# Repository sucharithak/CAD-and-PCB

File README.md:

# COMSOL- CAD-and-PCB
I created this repository to show the CAD and PCB designs I made during my student life as a hiwi. And I updated it with my recent COMSOL designs
This work was done over a span of few years.
I have learnt and unlearnt doing designs under many informative tutors, a.k.a my PHD and postdoc colleagues from the labs I have worked.
The main motivation in creating this repository is to include all my designs at a single place so that I can put a link in my CV.

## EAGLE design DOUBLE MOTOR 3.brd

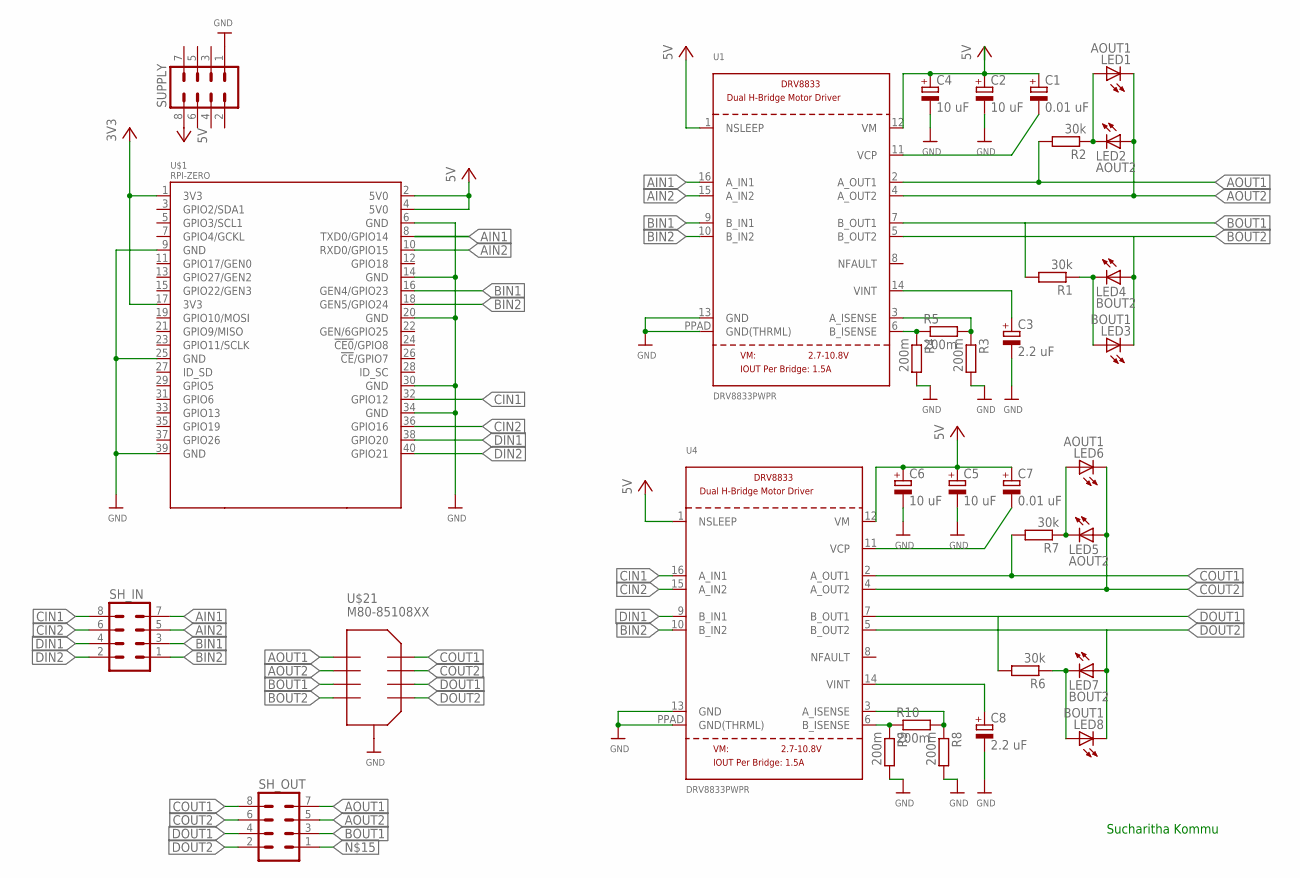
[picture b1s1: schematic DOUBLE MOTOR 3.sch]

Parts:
C1, C7: 0.01 uF; SMC_C
C2, C5: 10 uF; E2,5-6
C3, C8: 2.2 uF; SMC_C
C4, C6: 10 uF; E3,5-8
LED1, LED6: AOUT1; LED5MM
LED2, LED5: AOUT2; LED5MM
LED3, LED8: BOUT1; LED5MM
LED4, LED7: BOUT2; LED5MM
R1, R2, R6, R7: 30k; 0204V
R3, R4, R5, R8, R9, R10: 200m; 0204V
SH_IN: MA04-2
SH_OUT: MA04-2
SUPPLY: MA04-2
U1, U4: DRV8833PWPR; HTSSOP16
U$1: RPI-ZERO; RASPBERRYPI_BASTELSTUBE_V13_RASPI_BOARD_B+_FULL
U$21: M80-85108XX

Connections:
3V3: U$1.1 (3V3), U$1.17 (3V3)
5V: U$1.2 (5V0), U$1.4 (5V0)
AIN1: SH_IN.7, U1.16 (A_IN1), U$1.8 (TXD0/GPIO14)
AIN2: SH_IN.5, U1.15 (A_IN2), U$1.10 (RXD0/GPIO15)
AOUT1: R2.2, SH_OUT.7, U1.2 (A_OUT1), U$21.P$5
AOUT2: LED1.K (C), LED2.A, SH_OUT.5, U1.4 (A_OUT2), U$21.P$7
BIN1: SH_IN.3, U1.9 (B_IN1), U$1.16 (GEN4/GPIO23)
BIN2: SH_IN.1, U1.10 (B_IN2), U4.10 (B_IN2), U$1.18 (GEN5/GPIO24)
BOUT1: R1.2, SH_OUT.3, U1.7 (B_OUT1), U$21.P$9
BOUT2: LED3.K (C), LED4.A, U1.5 (B_OUT2), U$21.P$11
CIN1: SH_IN.8, U4.16 (A_IN1), U$1.32 (GPIO12)
CIN2: SH_IN.6, U4.15 (A_IN2), U$1.36 (GPIO16)
COUT1: R7.2, SH_OUT.8, U4.2 (A_OUT1), U$21.P$6
COUT2: LED5.A, LED6.K (C), SH_OUT.6, U4.4 (A_OUT2), U$21.P$8
DIN1: SH_IN.4, U4.9 (B_IN1), U$1.38 (GPIO20)
DIN2: SH_IN.2, U$1.40 (GPIO21)
DOUT1: R6.2, SH_OUT.4, U4.7 (B_OUT1), U$21.P$10
DOUT2: LED7.A, LED8.K (C), SH_OUT.2, U4.5 (B_OUT2), U$21.P$12
GND: C1.-, C2.-, C3.-, C4.-, C5.-, C6.-, C7.-, C8.-, R3.2, R4.2, R8.2, R9.2, SUPPLY.1, U1.11 (VCP), U1.13 (GND), U1.PPAD (GND(THRML)), U4.11 (VCP), U4.13 (GND), U4.PPAD (GND(THRML)), U$1.6 (GND), U$1.9 (GND), U$1.14 (GND), U$1.20 (GND), U$1.25 (GND), U$1.30 (GND), U$1.34 (GND), U$1.39 (GND), U$21.COMMON1 (COMMON), U$21.COMMON2 (COMMON), U$21.COMMON3 (COMMON), U$21.COMMON4 (COMMON)
unnamed: LED7.K (C), LED8.A, R6.1
unnamed: LED5.K (C), LED6.A, R7.1
unnamed: R8.1, R10.2, U4.3 (A_ISENSE)
unnamed: C8.+, U4.14 (VINT)
unnamed: LED1.A, LED2.K (C), R2.1
unnamed: R9.1, R10.1, U4.6 (B_ISENSE)
unnamed: LED3.A, LED4.K (C), R1.1
unnamed: C3.+, U1.14 (VINT)
unnamed: R3.1, R5.2, U1.3 (A_ISENSE)
unnamed: R4.1, R5.1, U1.6 (B_ISENSE)
VCC: C1.+, C2.+, C4.+, C5.+, C6.+, C7.+, SUPPLY.8, U1.1 (NSLEEP), U1.12 (VM), U4.1 (NSLEEP), U4.12 (VM)

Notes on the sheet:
Sucharitha Kommu

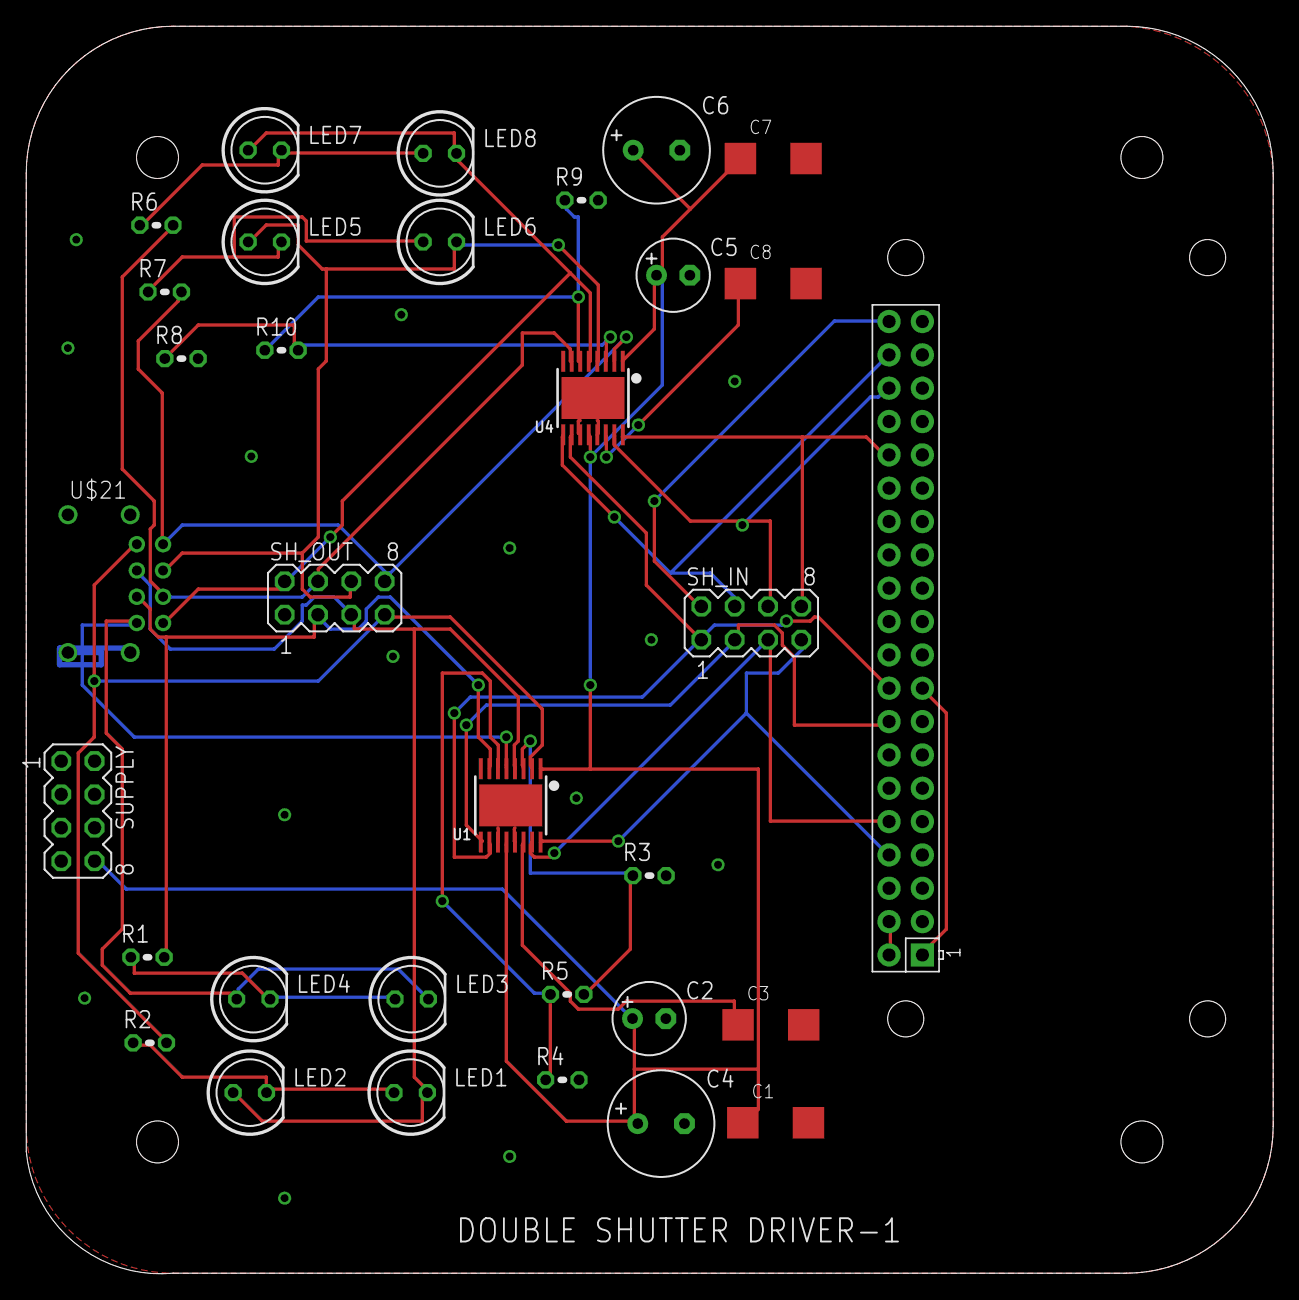
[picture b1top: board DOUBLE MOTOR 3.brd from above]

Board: 2 copper layers, 95.0 x 95.0 mm, 33 parts (0 on the bottom side), 30 nets.

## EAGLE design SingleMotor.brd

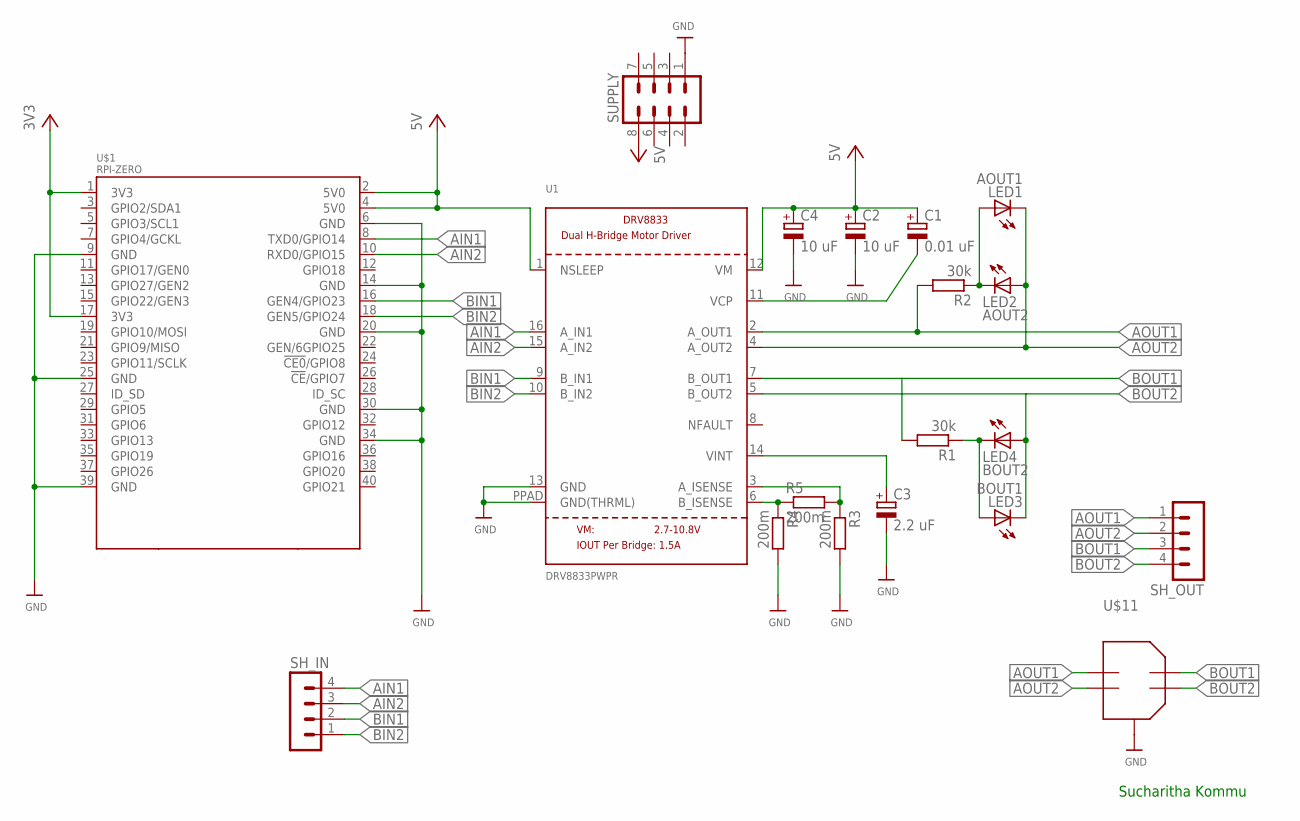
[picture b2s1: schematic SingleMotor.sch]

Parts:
C1: 0.01 uF; SMC_C
C2: 10 uF; E2,5-6
C3: 2.2 uF; SMC_C
C4: 10 uF; E3,5-8
LED1: AOUT1; LED5MM
LED2: AOUT2; LED5MM
LED3: BOUT1; LED5MM
LED4: BOUT2; LED5MM
R1, R2: 30k; 0204V
R3, R4, R5: 200m; 0204V
SH_IN: MA04-1
SH_OUT: MA04-1
SUPPLY: MA04-2
U1: DRV8833PWPR; HTSSOP16
U$1: RPI-ZERO; RASPBERRYPI_BASTELSTUBE_V13_RASPI_BOARD_B+_FULL
U$11: M80-85104XX"; M80-85104XX

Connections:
3V3: U$1.1 (3V3), U$1.17 (3V3)
5V: U1.1 (NSLEEP), U$1.2 (5V0), U$1.4 (5V0)
AIN1: SH_IN.4, U1.16 (A_IN1), U$1.8 (TXD0/GPIO14)
AIN2: SH_IN.3, U1.15 (A_IN2), U$1.10 (RXD0/GPIO15)
AOUT1: R2.2, SH_OUT.1, U1.2 (A_OUT1), U$11.P1
AOUT2: LED1.K (C), LED2.A, SH_OUT.2, U1.4 (A_OUT2), U$11.P3
BIN1: SH_IN.2, U1.9 (B_IN1), U$1.16 (GEN4/GPIO23)
BIN2: SH_IN.1, U1.10 (B_IN2), U$1.18 (GEN5/GPIO24)
BOUT1: R1.2, SH_OUT.3, U1.7 (B_OUT1), U$11.P2
BOUT2: LED3.K (C), LED4.A, SH_OUT.4, U1.5 (B_OUT2), U$11.P4
GND: C1.-, C2.-, C3.-, C4.-, R3.2, R4.2, SUPPLY.1, U1.11 (VCP), U1.13 (GND), U1.PPAD (GND(THRML)), U$1.6 (GND), U$1.9 (GND), U$1.14 (GND), U$1.20 (GND), U$1.25 (GND), U$1.30 (GND), U$1.34 (GND), U$1.39 (GND), U$11.CASE1 (CASE), U$11.CASE2 (CASE), U$11.CASE3 (CASE), U$11.CASE4 (CASE)
unnamed: LED1.A, LED2.K (C), R2.1
unnamed: LED3.A, LED4.K (C), R1.1
unnamed: C3.+, U1.14 (VINT)
unnamed: R3.1, R5.2, U1.3 (A_ISENSE)
unnamed: R4.1, R5.1, U1.6 (B_ISENSE)
VCC: C1.+, C2.+, C4.+, SUPPLY.8, U1.12 (VM)

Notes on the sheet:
Sucharitha Kommu

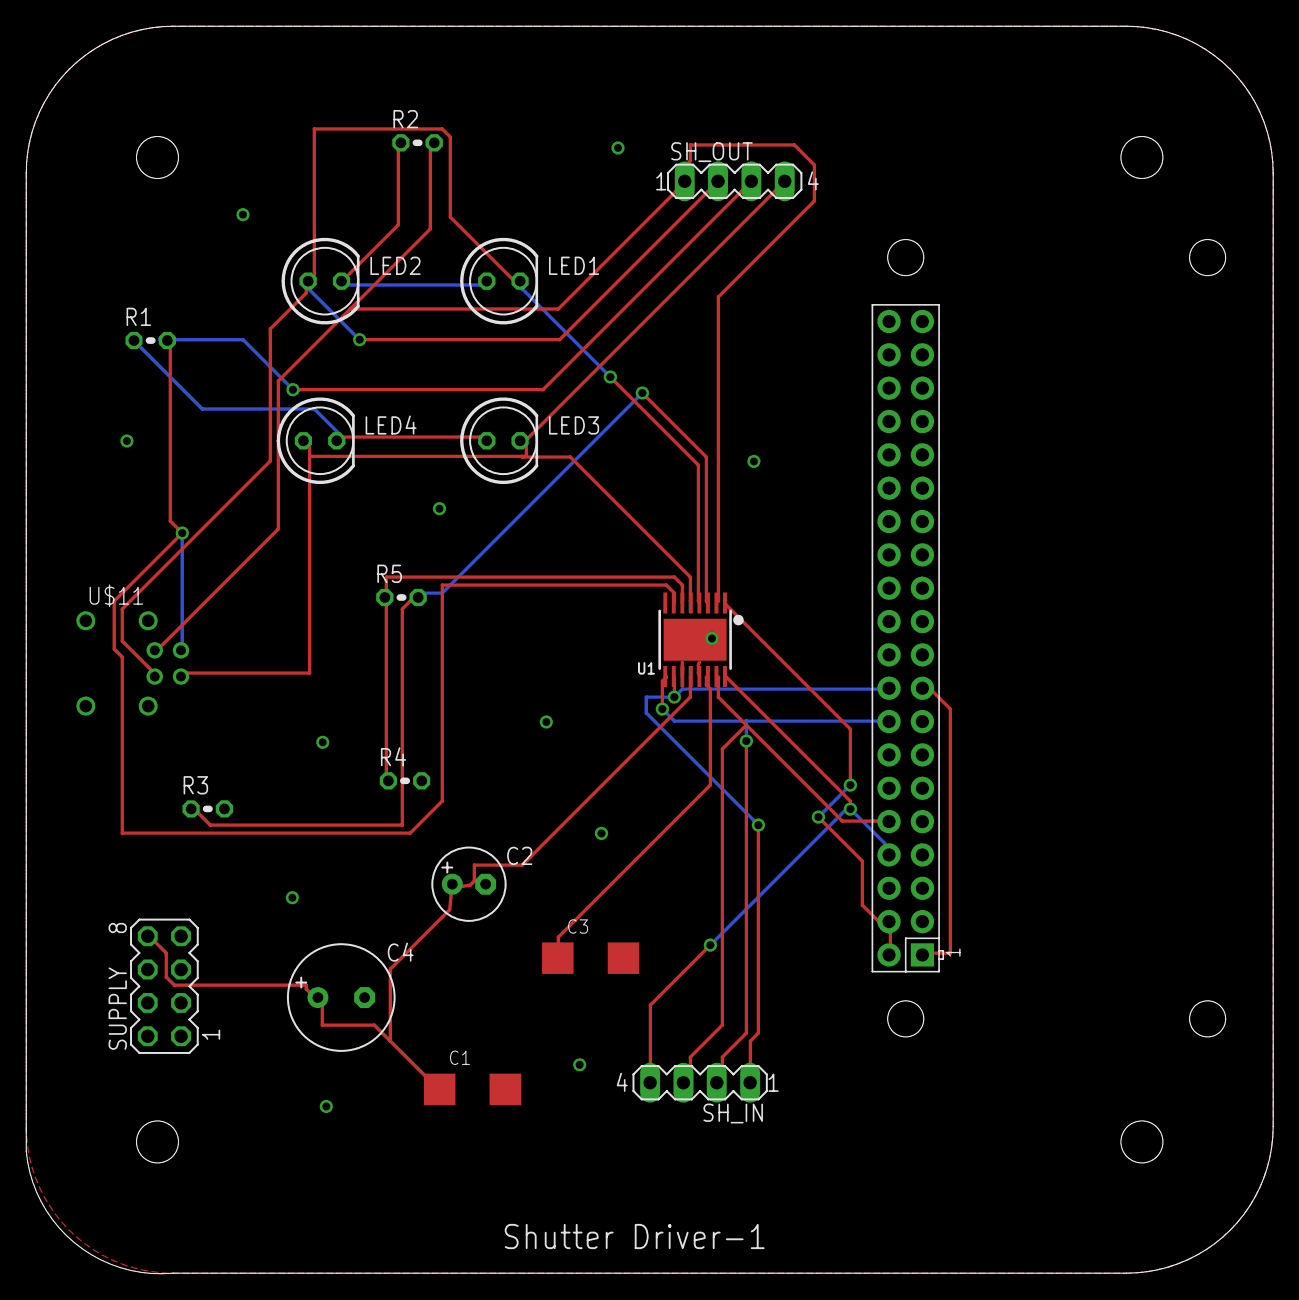
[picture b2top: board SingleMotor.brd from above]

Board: 2 copper layers, 95.0 x 95.0 mm, 19 parts (0 on the bottom side), 17 nets.

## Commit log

2024-02-16 Introduction to this repository
2026-05-20 Add files via upload
    COMSOL- Topology optimization of U_magnetic on a levitated graphite and surface of dU/dz on levitated graphite
2026-06-16 Add files via upload
    Abstract accepted 2026- Conference on Quantum levitated systems
2026-06-16 Add files via upload
    Presented poster at ESMRMB 2025 on Chipiron's Ultra low field MRI
